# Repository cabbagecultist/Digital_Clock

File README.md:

# A smart digital clock for the modern age

Are you tired of boring, simple clocks that just work? I am!
With this clock, you can display not only the time but also whatever unnecessary information that your heart desires!
I love it!!!

Just kidding, this sucks.

Features:
- Automatic time synchronisation with an NTP server, preventing the need for manually setting the time in case the RTC clock loses power.
- An RTC Module, ensuring that the clock stays functional even when not connected to the internet.
- SD Card support.
- A simple, modular menu system!

Adding screens to the menu is as easy as: 
- Subclassing the ```Screen``` class,
- Overriding the ```init()``` and ```draw()``` methods,
- Adding a pointer to an instance of your class to the ```modes``` vector in ```Digital_Clock.cpp``` !

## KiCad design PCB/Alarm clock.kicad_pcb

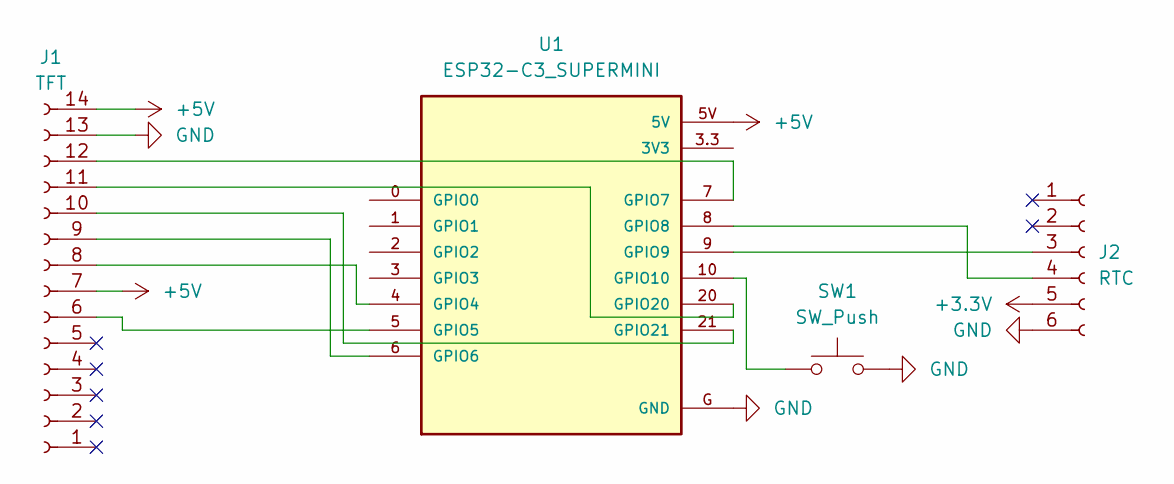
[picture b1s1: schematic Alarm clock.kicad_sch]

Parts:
J1: TFT; PinHeader_1x14_P2.54mm_Vertical
J2: RTC; PinHeader_1x06_P2.54mm_Vertical
SW1: SW_Push; SW_PUSH_6mm
U1: ESP32-C3_SUPERMINI; MODULE_ESP32-C3_SUPERMINI

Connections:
+3V3: J2.5
+5V: J1.7, J1.14, U1.5V
GND: J1.13, J2.6, SW1.2, U1.G (GND)
unnamed: J1.6, U1.5 (GPIO5)
unnamed: J1.8, U1.4 (GPIO4)
unnamed: J1.9, U1.6 (GPIO6)
unnamed: J1.10, U1.21 (GPIO21)
unnamed: J1.11, U1.20 (GPIO20)
unnamed: J1.12, U1.7 (GPIO7)
unnamed: J2.3, U1.9 (GPIO9)
unnamed: J2.4, U1.8 (GPIO8)
unnamed: SW1.1, U1.10 (GPIO10)

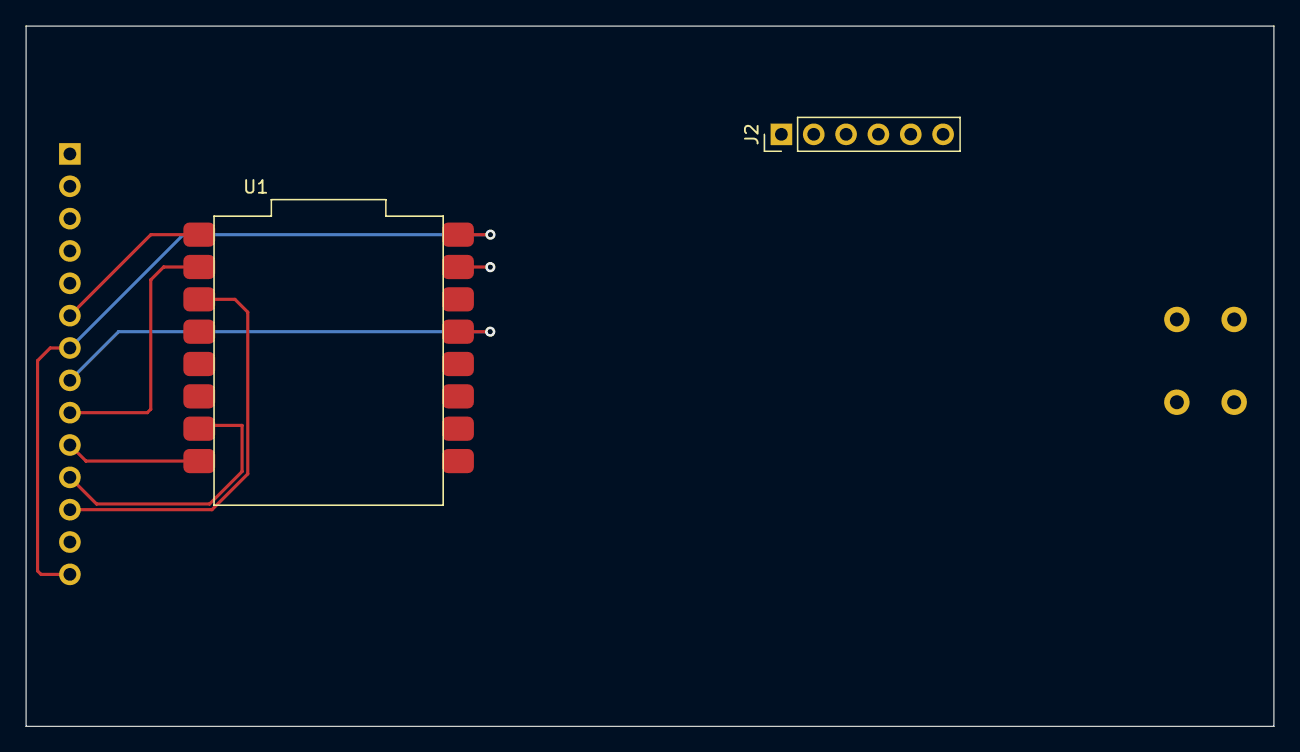
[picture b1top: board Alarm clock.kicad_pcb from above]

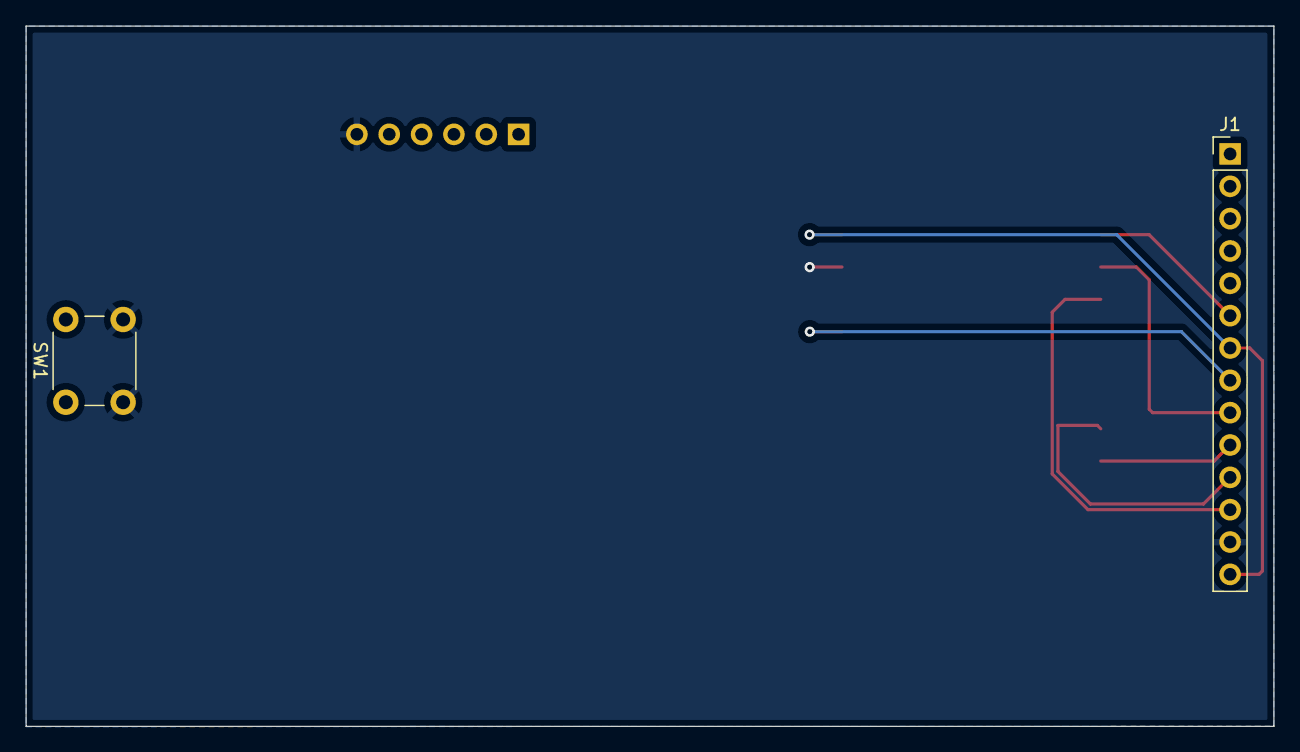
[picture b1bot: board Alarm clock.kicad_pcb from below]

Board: 4 copper layers, 98.0 x 55.0 mm, 4 parts (2 on the bottom side), 11 nets.

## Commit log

2024-06-23 Basic HTTP Request code, but looks like it doesn't work :(
2024-06-23 It worksgit add . The HTTPS Connection has to be insecure though.
2024-06-23 JSON deserializing works
2024-06-23 Fixed HTTPS Certs and requests being made constantly
2024-06-25 Basic lcd testing
2024-06-25 Stuff
2024-07-02 The menu works!
2024-07-05 Fixed clock display glitch, started working on displaying timezone-corrected time. Messed around with char arrays instead of Strings, which are supposedly better.
2024-07-06 Time till next rotation added
2024-07-06 Cleanup & Organisation
2024-07-06 Added photos & videos
2024-07-10 Printing normal time & time till next rotation on TFT display
2024-07-10 Basic UI
2024-07-12 Removed 16x2 LCD support and drawing on TFT screen only when necessary
2024-07-12 Showcase media
2024-07-12 Add PCB files
2024-07-18 Use Hardware SPI and start working on SD support
2024-07-19 Display test image (:3)
2024-07-19 Why can't I subclass
2024-07-20 Added different subclasses for modes, still a mess
2024-07-20 Easy addition & reordering of modesgit add .
2024-07-20 A few fixes
2024-07-21 PCB Update
